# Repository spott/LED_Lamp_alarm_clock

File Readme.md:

# An LED alarm clock.  

Also known as a ESP8266 controlled PWM driver, lowish power AC Dimmer, and relay driver.  The schematic is available in PDF form in the PDFs folder, along with the PCB layout.

The ESP controls three different things here:

In the top right of the board, there are two optocouplers.  The ESP reads the voltage across the AC line using the ADC pin, and turns on a triac with GPIO12 (the `AC_CTRL1` net).  It can also turn on an SSR, a relay switch or some other load using `AC_CTRL2`.  `AC_CTRL2` and associated circuitry is on the left underneath the SMPS.

The bottom of the board contains the PWM control chip.  It has 16 LED outputs, of which 15 are broken out, and drive low V_th, and low gate charge N channel MOSFETs.  These act as low side switches for the pins that are next to them.  At the moment, the limit on the current that each can drive is the connector is the connector I believe.

This board is driven by a 12V input on the left side of the board, above the relay output.  The 12V is guided around the outside of the board in a rather wide copper pour on the bottom of the board, and is also used as the Vin of a SMPS that generates the 3.3V power for the ESP and PWM chip.

## Programming the board:

The programming of the ESP is done with a push switch (when the LED is lighted, the board is ready to run, when it is off, the board is waiting to be programmed), and a reset switch (the switch pulls reset low).  When the board is waiting to be programmed, a low signal on the DTR pin of the FTDI cable pulls CH_PD low, along with GPIO0 (hopefully, in case the switch is in the wrong position).

## Software:

Kicad 4.0.4 mostly, though some work was done with Kicad Master branch.

If you have trouble opening it with Kicad 4.0.4, submit an issue and I'll take care of it.

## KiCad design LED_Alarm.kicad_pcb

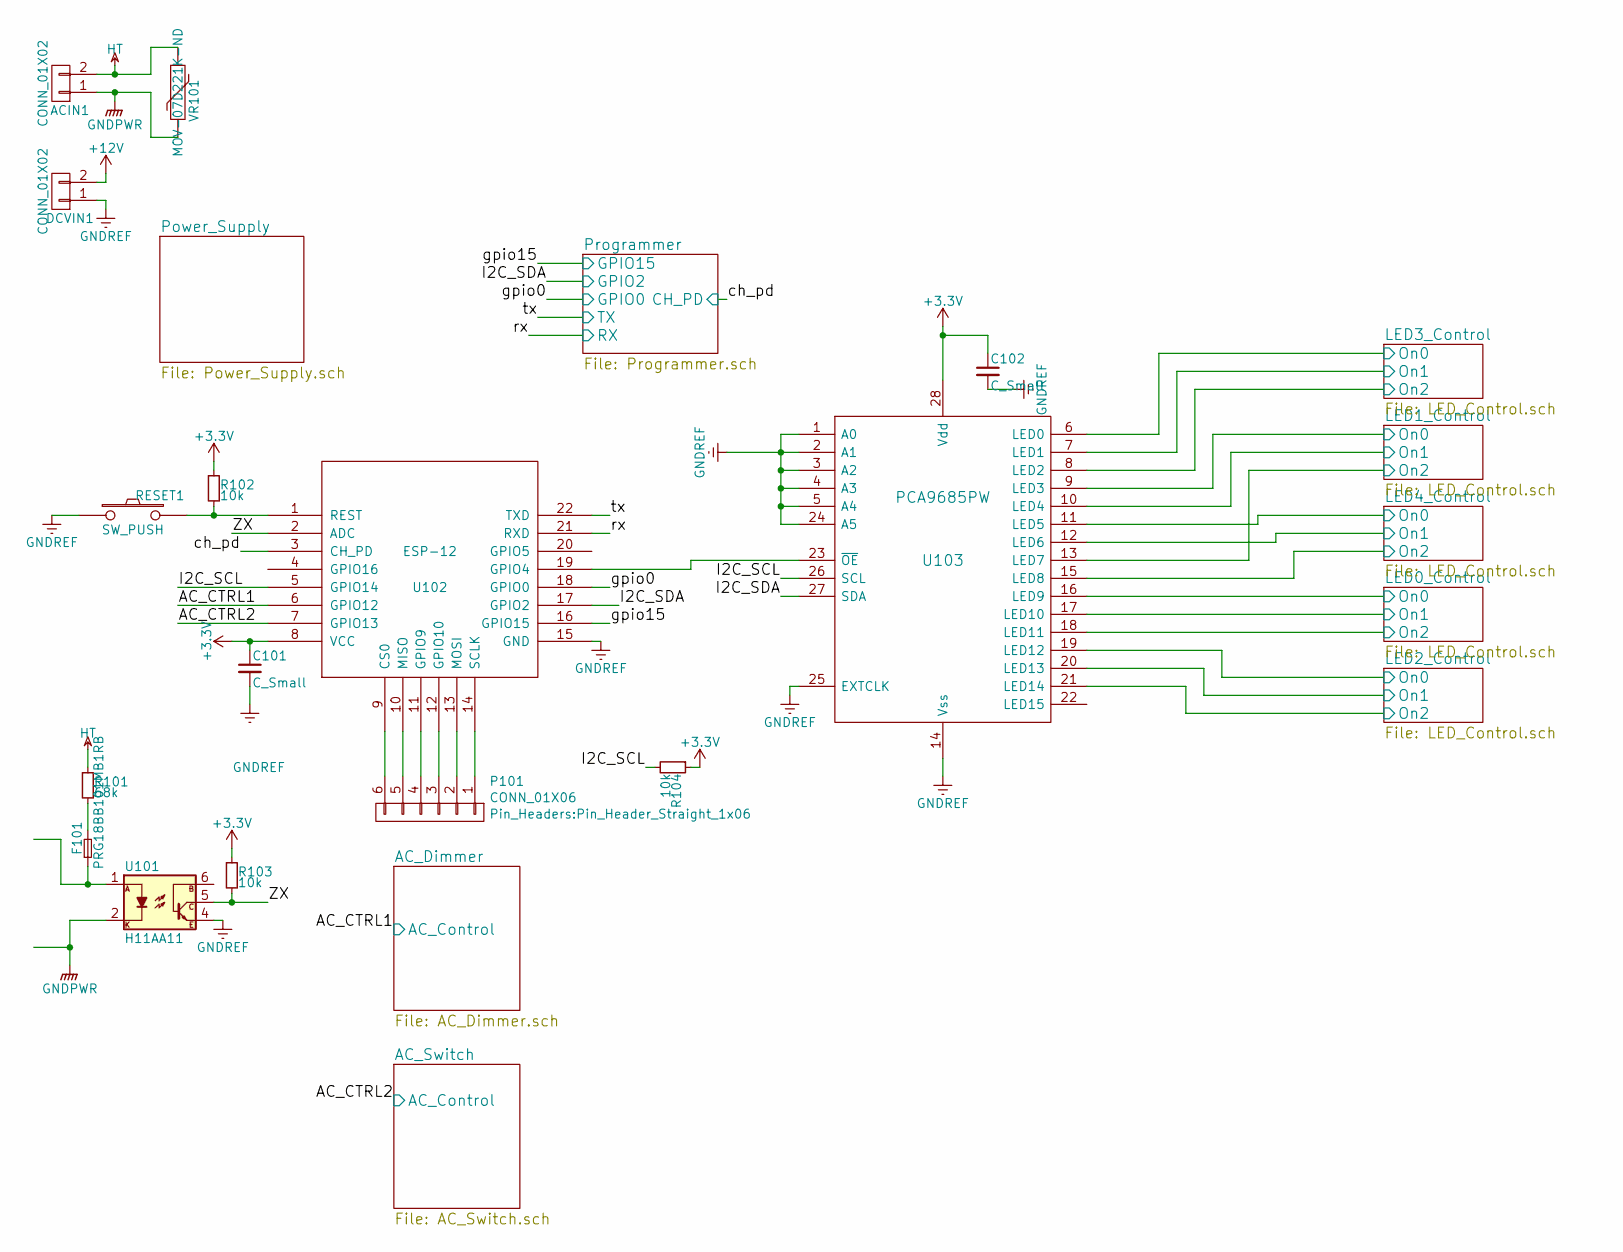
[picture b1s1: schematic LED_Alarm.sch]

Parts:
ACIN1: CONN_01X02; TerminalBlock_Pheonix_PT-3.5mm_2pol
C101, C102: C_Small; C_0603_HandSoldering
DCVIN1: CONN_01X02; TerminalBlock_Pheonix_MKDS1.5-2pol
F101: PRG18BB101MB1RB; R_0603_HandSoldering
P101: CONN_01X06; Pin_Header_Straight_1x06
R101: 68k; Resistor_Horizontal_RM10mm
R102, R103, R104: 10k; R_0603_HandSoldering
RESET1: SW_PUSH; SW_SPST_EVQQ2
U101: H11AA11; DIP-6_W7.62mm
U102: ESP-12; ESP-12E
U103: PCA9685PW; TSSOP-28_4.4x9.7mm_Pitch0.65mm
VR101: MOV-07D221K-ND; RV_Disc_D9_W3.5_P5

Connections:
+3V3: C101.1, C102.1, R102.1, R103.1, R104.1, U102.8 (VCC), U103.28 (Vdd); also elsewhere on the board
+12V: DCVIN1.2; also elsewhere on the board
/AC_CTRL1: U102.6 (GPIO12); also elsewhere on the board
/AC_CTRL2: U102.7 (GPIO13); also elsewhere on the board
/I2C_SCL: R104.2, U102.5 (GPIO14), U103.26 (SCL)
/I2C_SDA: U102.17 (GPIO2), U103.27 (SDA); also elsewhere on the board
/LED0_Control/On0: U103.16 (LED9); also elsewhere on the board
/LED0_Control/On1: U103.17 (LED10); also elsewhere on the board
/LED0_Control/On2: U103.18 (LED11); also elsewhere on the board
/LED1_Control/On0: U103.9 (LED3); also elsewhere on the board
/LED1_Control/On1: U103.10 (LED4); also elsewhere on the board
/LED1_Control/On2: U103.13 (LED7); also elsewhere on the board
/LED2_Control/On0: U103.19 (LED12); also elsewhere on the board
/LED2_Control/On1: U103.20 (LED13); also elsewhere on the board
/LED2_Control/On2: U103.21 (LED14); also elsewhere on the board
/LED3_Control/On0: U103.6 (LED0); also elsewhere on the board
/LED3_Control/On1: U103.7 (LED1); also elsewhere on the board
/LED3_Control/On2: U103.8 (LED2); also elsewhere on the board
/LED4_Control/On0: U103.11 (LED5); also elsewhere on the board
/LED4_Control/On1: U103.12 (LED6); also elsewhere on the board
/LED4_Control/On2: U103.15 (LED8); also elsewhere on the board
/ZX: R103.2, U101.5, U102.2 (ADC)
/ch_pd: U102.3 (CH_PD); also elsewhere on the board
/gpio0: U102.18 (GPIO0); also elsewhere on the board
/gpio15: U102.16 (GPIO15); also elsewhere on the board
/rx: U102.21 (RXD); also elsewhere on the board
/tx: U102.22 (TXD); also elsewhere on the board
GNDPWR: ACIN1.1, U101.2, VR101.2; also elsewhere on the board
GNDREF: C101.2, C102.2, DCVIN1.1, RESET1.1, U101.4, U102.15 (GND), U103.1 (A0), U103.2 (A1), U103.3 (A2), U103.4 (A3), U103.5 (A4), U103.14 (Vss), U103.24 (A5), U103.25 (EXTCLK); also elsewhere on the board
HT: ACIN1.2, R101.1, VR101.1; also elsewhere on the board
unnamed: F101.1, U101.1
unnamed: F101.2, R101.2
unnamed: P101.1, U102.14 (SCLK)
unnamed: P101.2, U102.13 (MOSI)
unnamed: P101.3, U102.12 (GPIO10)
unnamed: P101.4, U102.11 (GPIO9)
unnamed: P101.5, U102.10 (MISO)
unnamed: P101.6, U102.9 (CS0)
unnamed: R102.2, RESET1.2, U102.1 (REST)
unnamed: U102.19 (GPIO4), U103.23 (~OE)

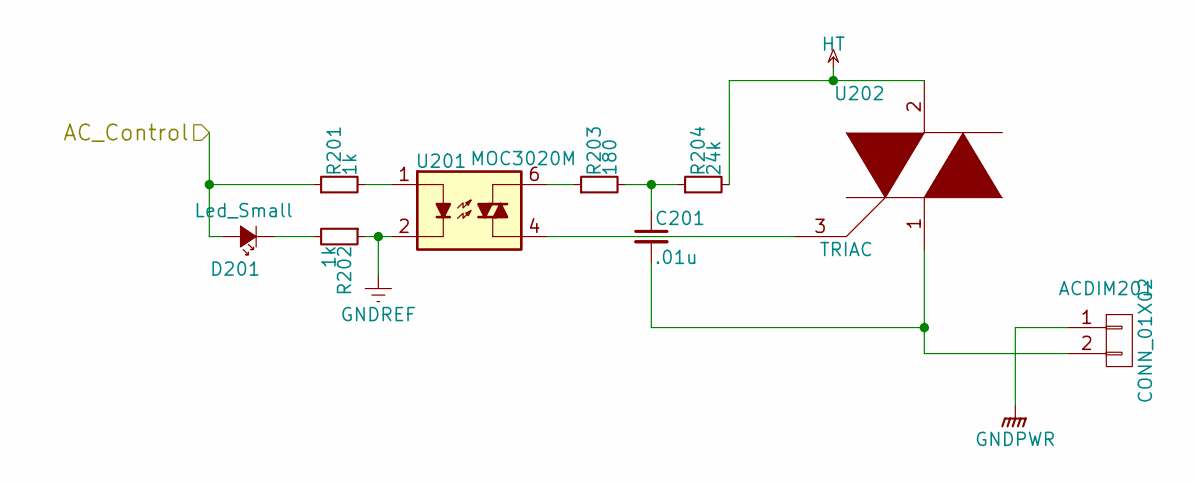
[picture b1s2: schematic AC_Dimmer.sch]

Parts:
ACDIM201: CONN_01X02; TerminalBlock_Pheonix_PT-3.5mm_2pol
C201: .01u; C_Rect_L7_W2.5_P5
D201: Led_Small; LED_0603
R201, R202: 1k; R_0603_HandSoldering
R203: 180; Resistor_Horizontal_RM10mm
R204: 24k; Resistor_Horizontal_RM10mm
U201: MOC3020M; DIP-6_W7.62mm
U202: TRIAC; TO-220_Neutral123_Vertical

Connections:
/AC_CTRL1: D201.2 (A), R201.1; also elsewhere on the board
GNDPWR: ACDIM201.1; also elsewhere on the board
GNDREF: R202.1, U201.2; also elsewhere on the board
HT: R204.2, U202.2; also elsewhere on the board
unnamed: ACDIM201.2, C201.2, U202.1
unnamed: C201.1, R203.2, R204.1
unnamed: D201.1 (K), R202.2
unnamed: R201.2, U201.1
unnamed: R203.1, U201.6
unnamed: U201.4, U202.3

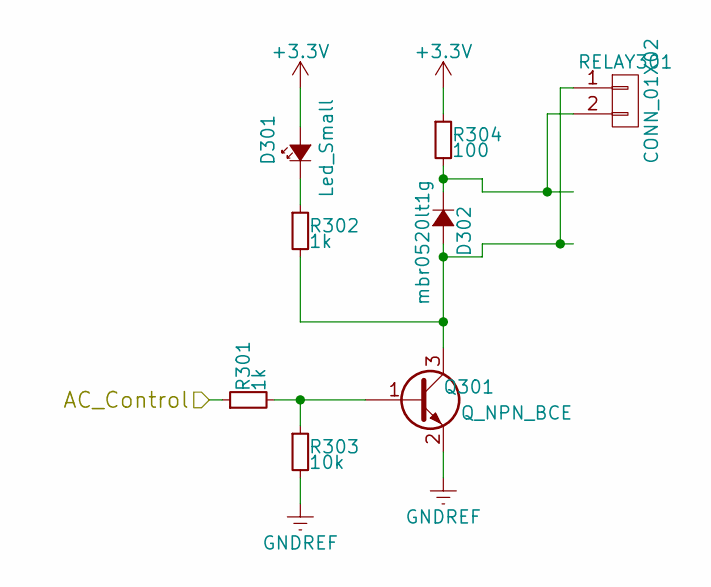
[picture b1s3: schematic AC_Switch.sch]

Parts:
D301: Led_Small; LED_0603
D302: mbr0520lt1g; SOD-123
Q301: Q_NPN_BCE; SOT-23_Handsoldering
R301, R302: 1k; R_0603_HandSoldering
R303: 10k; R_0603_HandSoldering
R304: 100; R_0603_HandSoldering
RELAY301: CONN_01X02; Pin_Header_Straight_1x02

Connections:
+3V3: D301.2 (A), R304.1; also elsewhere on the board
/AC_CTRL2: R301.1; also elsewhere on the board
GNDREF: Q301.2 (E), R303.2; also elsewhere on the board
unnamed: D301.1 (K), R302.1
unnamed: D302.1 (K), R304.2, RELAY301.2
unnamed: D302.2 (A), Q301.3 (C), R302.2, RELAY301.1
unnamed: Q301.1 (B), R301.2, R303.1

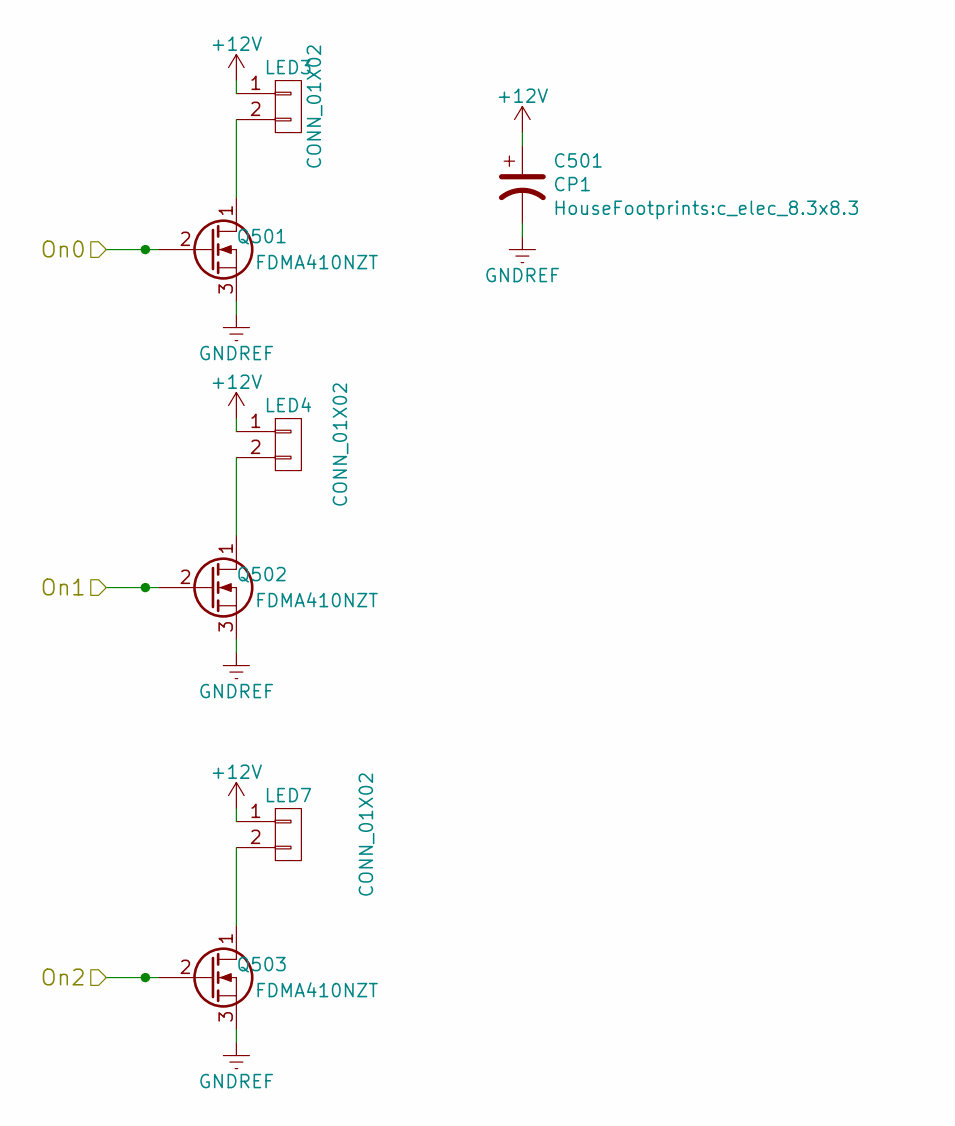
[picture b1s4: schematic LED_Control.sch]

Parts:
C401: CP1; c_elec_8.3x8.3
LED9, LED10, LED11: CONN_01X02; Pin_Header_Straight_1x02
Q401, Q402, Q403: FDMA410NZT; MicroFET-6

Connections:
+12V: C401.1, LED9.1, LED10.1, LED11.1; also elsewhere on the board
/LED0_Control/On0: Q401.2 (G); also elsewhere on the board
/LED0_Control/On1: Q402.2 (G); also elsewhere on the board
/LED0_Control/On2: Q403.2 (G); also elsewhere on the board
GNDREF: C401.2, Q401.3 (S), Q402.3 (S), Q403.3 (S); also elsewhere on the board
unnamed: LED9.2, Q401.1 (D)
unnamed: LED10.2, Q402.1 (D)
unnamed: LED11.2, Q403.1 (D)

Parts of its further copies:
C501, C601, C701, C801: CP1; c_elec_8.3x8.3
LED0, LED1, LED2, LED3, LED4, LED5, LED6, LED7, LED8, LED12, LED13, LED14: CONN_01X02; Pin_Header_Straight_1x02
Q501, Q502, Q503, Q601, Q602, Q603, Q701, Q702, Q703, Q801, Q802, Q803: FDMA410NZT; MicroFET-6

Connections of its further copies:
+12V: C501.1, C601.1, C701.1, C801.1, LED0.1, LED1.1, LED2.1, LED3.1, LED4.1, LED5.1, LED6.1, LED7.1, LED8.1, LED12.1, LED13.1, LED14.1; also elsewhere on the board
/LED1_Control/On0: Q501.2 (G); also elsewhere on the board
/LED1_Control/On1: Q502.2 (G); also elsewhere on the board
/LED1_Control/On2: Q503.2 (G); also elsewhere on the board
/LED2_Control/On0: Q601.2 (G); also elsewhere on the board
/LED2_Control/On1: Q602.2 (G); also elsewhere on the board
/LED2_Control/On2: Q603.2 (G); also elsewhere on the board
/LED3_Control/On0: Q701.2 (G); also elsewhere on the board
/LED3_Control/On1: Q702.2 (G); also elsewhere on the board
/LED3_Control/On2: Q703.2 (G); also elsewhere on the board
/LED4_Control/On0: Q801.2 (G); also elsewhere on the board
/LED4_Control/On1: Q802.2 (G); also elsewhere on the board
/LED4_Control/On2: Q803.2 (G); also elsewhere on the board
GNDREF: C501.2, C601.2, C701.2, C801.2, Q501.3 (S), Q502.3 (S), Q503.3 (S), Q601.3 (S), Q602.3 (S), Q603.3 (S), Q701.3 (S), Q702.3 (S), Q703.3 (S), Q801.3 (S), Q802.3 (S), Q803.3 (S); also elsewhere on the board
unnamed: LED0.2, Q701.1 (D)
unnamed: LED1.2, Q702.1 (D)
unnamed: LED2.2, Q703.1 (D)
unnamed: LED3.2, Q501.1 (D)
unnamed: LED4.2, Q502.1 (D)
unnamed: LED5.2, Q801.1 (D)
unnamed: LED6.2, Q802.1 (D)
unnamed: LED7.2, Q503.1 (D)
unnamed: LED8.2, Q803.1 (D)
unnamed: LED12.2, Q601.1 (D)
unnamed: LED13.2, Q602.1 (D)
unnamed: LED14.2, Q603.1 (D)

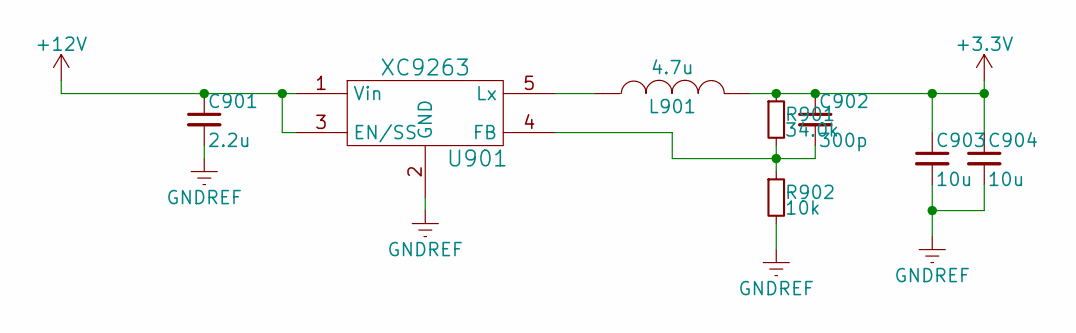
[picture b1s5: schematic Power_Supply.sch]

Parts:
C901: 2.2u; C_0603_HandSoldering
C902: 300p; C_0603_HandSoldering
C903, C904: 10u; C_0603_HandSoldering
L901: 4.7u; CLF6045NI-D-Inductor
R901: 34.0k; R_0603_HandSoldering
R902: 10k; R_0603_HandSoldering
U901: XC9263; SOT-25

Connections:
+3V3: C902.1, C903.1, C904.1, L901.2, R901.1; also elsewhere on the board
+12V: C901.1, U901.1 (Vin), U901.3 (EN/SS); also elsewhere on the board
GNDREF: C901.2, C903.2, C904.2, R902.2, U901.2 (GND); also elsewhere on the board
unnamed: C902.2, R901.2, R902.1, U901.4 (FB)
unnamed: L901.1, U901.5 (Lx)

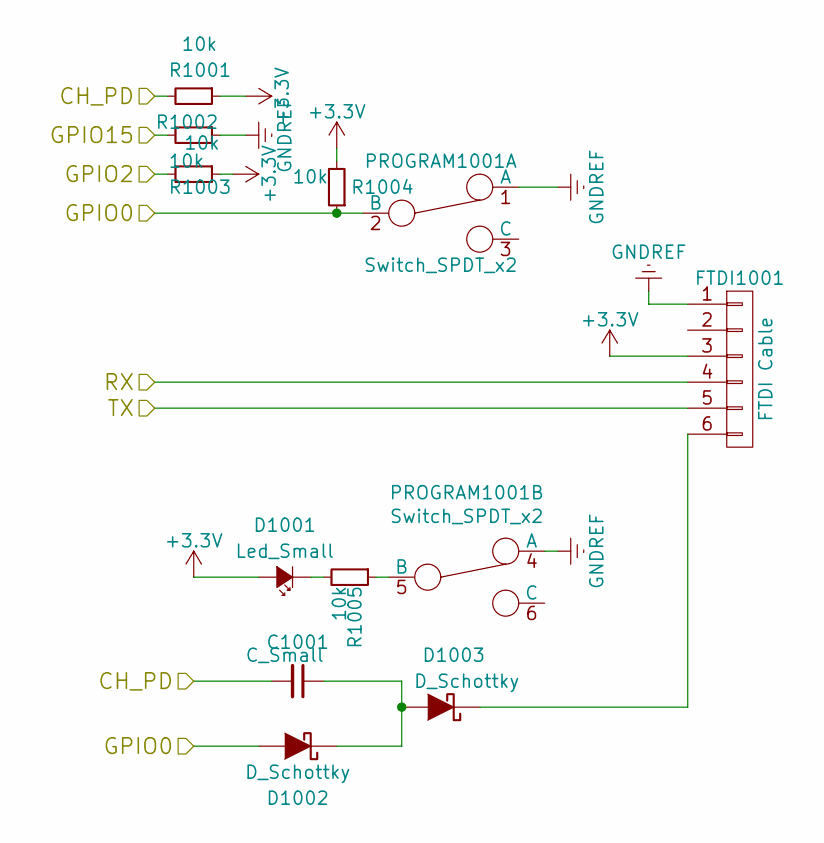
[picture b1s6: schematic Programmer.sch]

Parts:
C1001: C_Small; C_0603_HandSoldering
D1001: Led_Small; LED_0603
D1002, D1003: D_Schottky; SOD-323
FTDI1001: FTDI Cable; Pin_Header_Straight_1x06
PROGRAM1001: Switch_SPDT_x2; SW_PUSH_DPDT
R1001, R1002, R1003, R1004, R1005: 10k; R_0603_HandSoldering

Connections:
+3V3: D1001.2 (A), FTDI1001.3, R1001.1, R1003.1, R1004.2; also elsewhere on the board
/I2C_SDA: R1003.2; also elsewhere on the board
/ch_pd: C1001.2, R1001.2; also elsewhere on the board
/gpio0: D1002.2 (A), PROGRAM1001.2 (B), R1004.1; also elsewhere on the board
/gpio15: R1002.2; also elsewhere on the board
/rx: FTDI1001.4; also elsewhere on the board
/tx: FTDI1001.5; also elsewhere on the board
GNDREF: FTDI1001.1, PROGRAM1001.1 (A), PROGRAM1001.4 (A), R1002.1; also elsewhere on the board
unnamed: C1001.1, D1002.1 (K), D1003.2 (A)
unnamed: D1001.1 (K), R1005.2
unnamed: D1003.1 (K), FTDI1001.6
unnamed: PROGRAM1001.5 (B), R1005.1

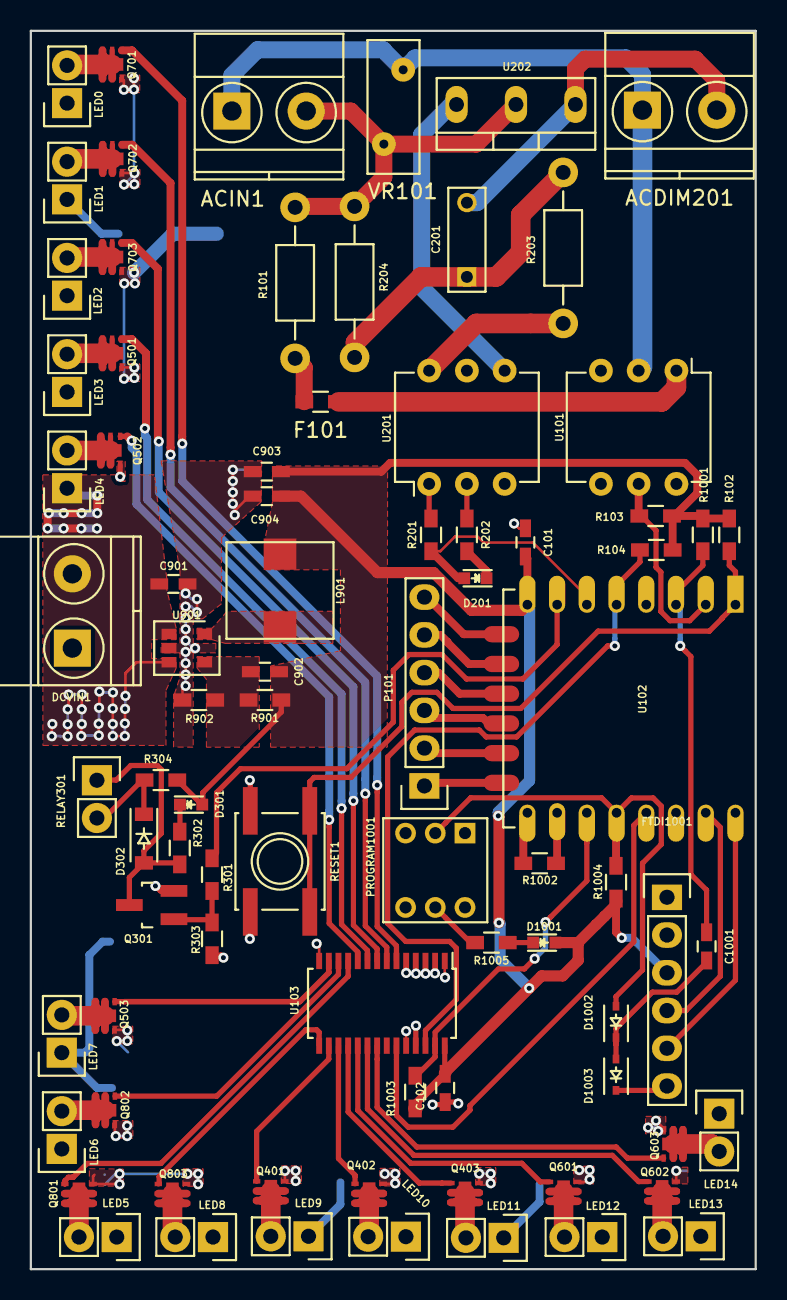
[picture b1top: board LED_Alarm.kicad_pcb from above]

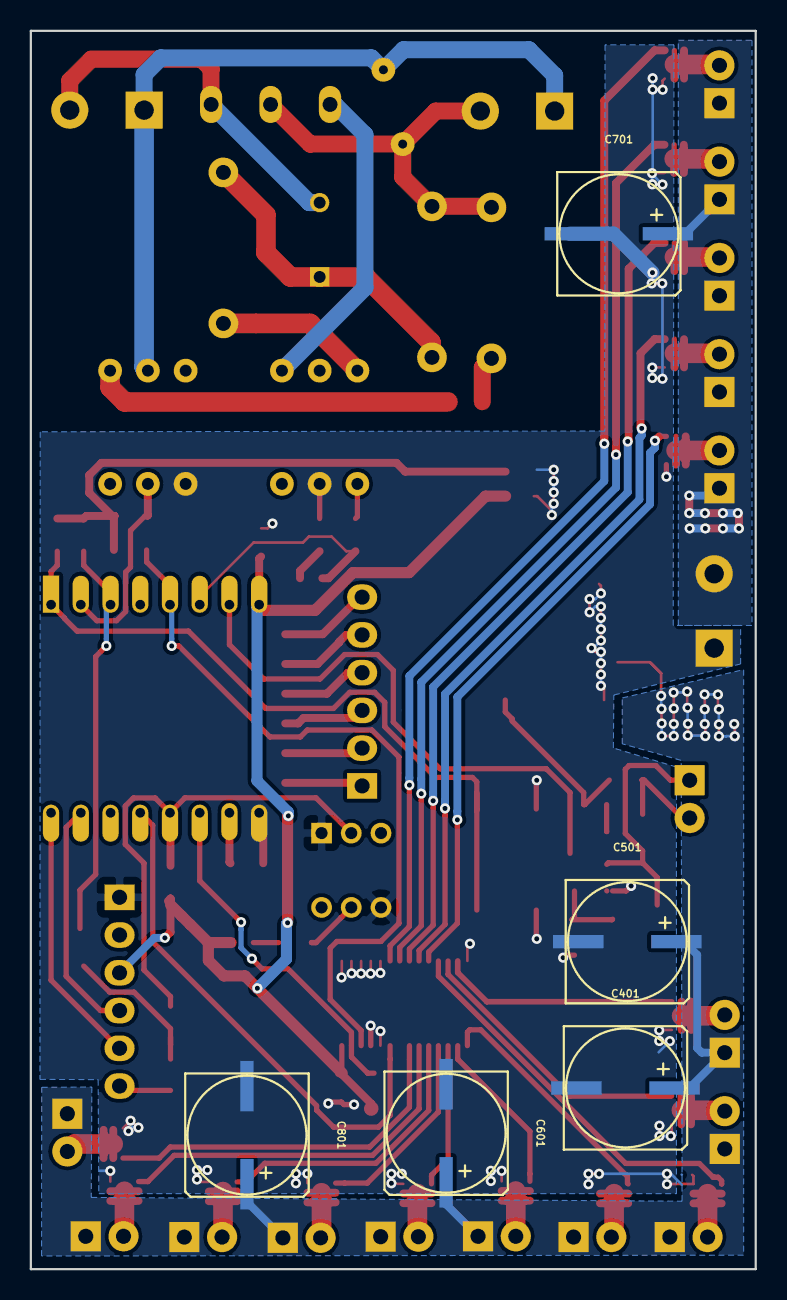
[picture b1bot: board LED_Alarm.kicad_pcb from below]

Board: 2 copper layers, 48.8 x 83.3 mm, 86 parts (5 on the bottom side), 71 nets.

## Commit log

2016-09-24 initial commit, pretty much done
2016-09-24 modified gitignore to ignore gerber files
2016-09-24 added a readme
2016-09-26 After changes suggested in https://www.reddit.com/r/PrintedCircuitBoard/comments/54ctxv/pcb_review_of_a_pwm_esp8266_led_driver_board/
2016-10-29 changed some stuff around
